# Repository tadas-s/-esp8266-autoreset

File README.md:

# FTDI cable adapter with dtrset reset method

Schematic taken from [this blog post][1]. The only small difference is output header pins drops
CTS and RTS pins and replaces with FLASH and RESET signals.

So board input is a standard FTDI 6 pin cable and output is:

    pin 1 -> GND
    pin 2 -> FLASH (to be connected to GPIO0)
    pin 3 -> VCC
    pin 4 -> TXD
    pin 5 -> RXD
    pin 6 -> RESET (to be connected to reset pin)

Project mentioned above exposes FLASH and RESET as a separate 2 pin header.

Schematic preview:

![schematic preview][2]

Complete and tested board:

![board][3]

Schematic captured and PCB done using the amazing [KiCad][1]!.

[1]: http://www.jce.lu/blog/?p=143 
[2]: autoreset-schematic-preview.png
[3]: board-photo.jpg
[4]: http://kicad-pcb.org/

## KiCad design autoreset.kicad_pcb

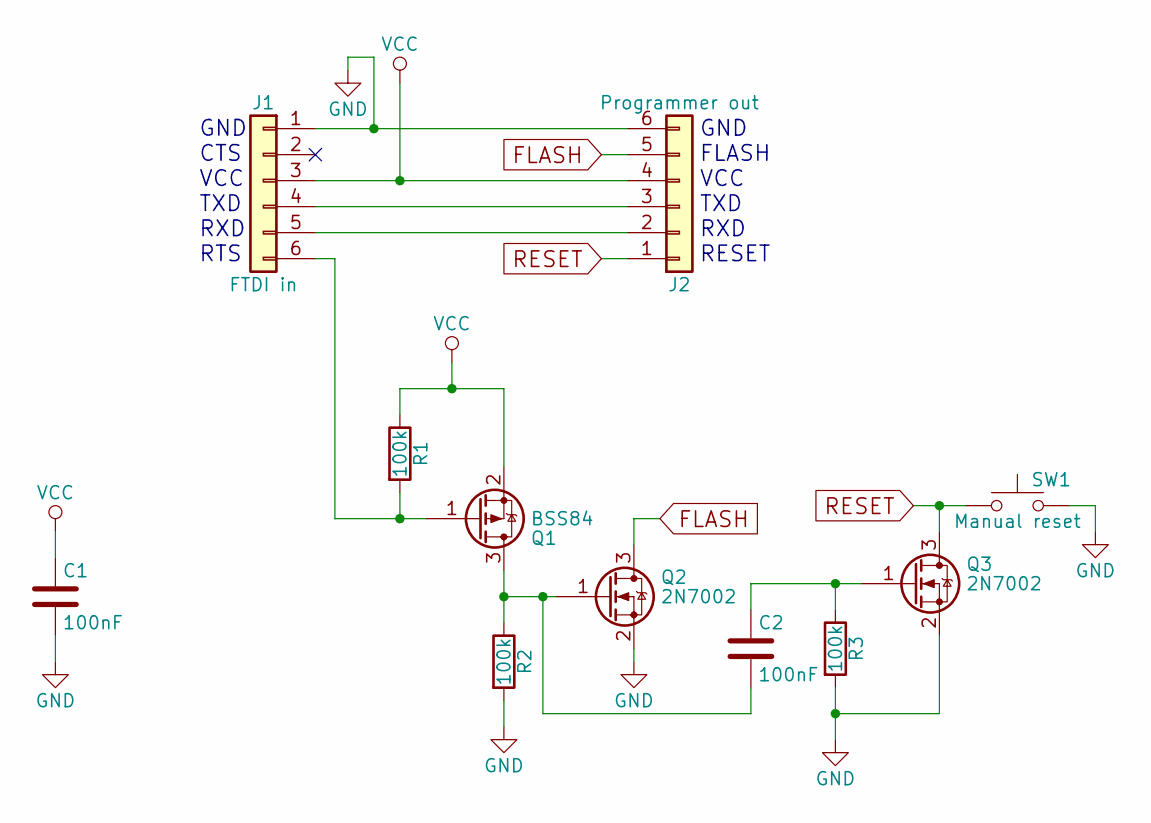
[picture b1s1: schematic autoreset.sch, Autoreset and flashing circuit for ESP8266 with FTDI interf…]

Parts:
C1, C2: 100nF; C_0805_HandSoldering
J1: FTDI in; Pin_Header_Angled_1x06_Pitch2.54mm
J2: Programmer out; Pin_Header_Angled_1x06_Pitch2.54mm
Q1: BSS84; SOT-23_Handsoldering
Q2, Q3: 2N7002; SOT-23_Handsoldering
R1, R2, R3: 100k; R_0805_HandSoldering
SW1: Manual reset; SW_SPST_PTS645

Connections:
FLASH: J2.5, Q2.3 (D)
GND: C1.2, J1.1, J2.6, Q2.2 (S), Q3.2 (S), R2.2, R3.2, SW1.2
unnamed: C2.1, Q3.1 (G), R3.1
unnamed: C2.2, Q1.3 (D), Q2.1 (G), R2.1
unnamed: J1.4, J2.3
unnamed: J1.5, J2.2
unnamed: J1.6, Q1.1 (G), R1.2
RESET: J2.1, Q3.3 (D), SW1.1
VCC: C1.1, J1.3, J2.4, Q1.2 (S), R1.1

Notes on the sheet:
GND CTS VCC TXD RXD RTS
GND FLASH VCC TXD RXD RESET

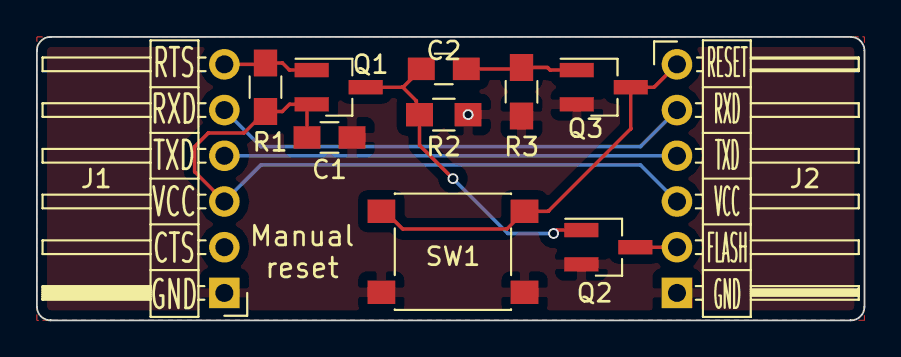
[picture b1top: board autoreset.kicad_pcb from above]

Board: 2 copper layers, 46.0 x 15.7 mm, 11 parts (0 on the bottom side), 9 nets.

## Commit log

2018-05-16 ESP8266 programmer with auto-reset
2018-05-17 Moving around some stuff to look nicer, no real change
2018-05-17 Add README.md with some references and previews
